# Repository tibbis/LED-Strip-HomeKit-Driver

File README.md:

# Siri Controlled RGB LED-Strip Project
#### By Thibault and Ramtin
### DIY RGB LED strip driver that can be connected to a smart home (HomeKit) using Raspberry Pi and Arduino.

This is a complete DIY guide going through all steps on how to build your own RGB LED Strip Driver that will be able to work together with Apple HomeKit. This will allow you to control the LED-strip wirelessly through the use of Siri. You simply tell Siri to turn on your LED-strip and set the color to e.g. red and through the combined work of the Raspberry Pi, Arduino Uno and a nicely crafted board, the strip will light up in the color of your choice.

_"Hey Siri, put my LED Strip to red."_

### Overview
This illustrates briefly how the complete system works. Basically, by giving Siri or HomeKit on an Apple device a command, the command will be passed to a homebridge server running on the Raspberry Pi. This command will then be passed to a local node.js server that will execute a program which in-turn will send color data wirelessly to an Arduino that is controlling a LED strip.

#### Components used for this project
- RGB-LED Strip (5m with 4 pins)
- Raspberry Pi 3 Model B+
- Arduino UNO
- 2x NRF24L01+ Radio transceiver
- 3x N-Channel MOSFET transistors (IRLB8721, BUZ100 or similar)
- 3x 160 Ohm Resistors
- Circuit Board or breadboard

You may use any type of N-Channel MOSFET as long as they can handle the amount of current that your LED-strip requires per color channel.

### Design of the circuit board for the LED-strip
Depending on your resources you can create your PCB as you want as long you follow the following schematic: (rgb-board.sch)

We will provide an EAGLE file so that it can be milled on a double-sided copper plate using a PCB milling machine, but if you lack the resources, we will also include illustrative pictures of how to do all of this using traditional breadboards.

If you are using a breadboard, this image can be helpful:

The left you see the EAGLE Board file design (rgb-board.brd) and to the right the result with the soldered transistors and resistors:

Now that the LED strip has been prepared with the Arduino, we will take a look at how to hook it up with the RF24-module to enable receiving signals from the Raspberry Pi.
#### Connecting RF24 transceiver to Arduino

This image shows how to connect the wireless transceiver to the Arduino pins.

##### Implementation of code on Arduino
The following code is then implemented into the Arduino. (RGB_DRIVER.ino). Please note that the library RF24.h needs to be installed from e.g: https://github.com/maniacbug/RF24. The pins corresponds to the same pins as the pictures above and the same ID set to the parameter```const uint64_t pipe``` (i.e. in our case: 0xF0F0F0F0E1LL) will be used later on the Raspberry Pi program.

```Arduino
#include "nRF24L01.h"
#include "RF24.h"
#include "RF24_config.h"
#include <SPI.h>
/////////////////////////////-RF24-////////////////////////////////////////
RF24 radio(9, 10); //RF24 pins
const uint64_t pipe = 0xF0F0F0F0E1LL; //ID
unsigned long RGB = 0;
/////////////////////////////////////////////////////////////////////////

//////////////////////////////-RGB-/////////////////////////////////////////
#define REDPIN 5
#define GREENPIN 6
#define BLUEPIN 3
#define FADESPEED 1     // make this higher to slow down fading
int r, g, b, rPrev, gPrev, bPrev, f = 0;
int blueMask = 0xFF0000, greenMask = 0xFF00, redMask = 0xFF; //decoding masks
//////////////////////////////////////////////////////////////////////////

void setup(void) {

  //Radio module setup
  radio.begin();
  radio.openReadingPipe(1, pipe);
  radio.startListening();

  //RGB setup
  pinMode(REDPIN, OUTPUT);
  pinMode(GREENPIN, OUTPUT);
  pinMode(BLUEPIN, OUTPUT);

  //serial Setup
  Serial.begin(9600);
  Serial.println("Started Listening...");
}

void loop(void)
{

  if (radio.available()) { //signal received

    if ( !radio.read(&RGB, sizeof(unsigned long)) ) {
      Serial.println("ACK not received by client.");
    }

    //save previous values
    rPrev = r;
    gPrev = g;
    bPrev = b;
    int[3] prevColors = [rPrev, gPrev, bPrev]; //array with previous color values

    //decode RGB values
    r = (RGB & 0xFF);
    g = ((RGB & 0xFF00) >> 8);
    b = ((RGB & 0xFF0000) >> 16);
    int[3] colors = [r,g,b]; //array with color values

    Serial.print("Received RGB-value: R= "); Serial.print(r); Serial.print(", G= ");
    Serial.print(g); Serial.print(", B= "); Serial.println(b);

    //change color with a smooth transition
    changeColor(colors, prevColors);

  }
}

//change color with a smooth transition
void changeColor(int[3] colors, int[3]prevColors){
  //To determine increase or decrease
  int diffR = colors[0]-prevColors[0];
  int diffG = colors[1]-prevColors[1];
  int diffB = colors[2]-prevColors[2];

  int i = prevColors[0];
  int j = prevColors[1];
  int k = prevColors[2];

  while (i==r && j==g && k==b)
  {
    //Red color
    if (i!=r){
      if (diffR>0) i++;
      else  i--;
      analogWrite(REDPIN, i);

    }
    //Green color
    if (k!=g){
      if (diffG>0) j++;
      else  j--;
      analogWrite(GREENPIN, j);
    }
    //Blue color
    if (k!=b){
      if (diffB>0) k++;
      else  k--;
      analogWrite(BLUEPIN, k);
    }
    delay(FADESPEED);
  }
}
```

### Design and create your own box
We provide you 3D CAD files for a 3D-printable box that fits an Arduino UNO and our PCB that we used. Depending on your circuit board dimensions you may need to create your own box. It needs 3 openings, one for the Arduino USB and DC inputs, and one RGB-LED strip output port (in our case 4 pins). The box should contain the Arduino, circuit board and RF24 transceiver with all its wires.

### Connecting RF24-transceiver to Raspberry Pi 3 B+
When the homebridge and node.js servers are running on the Raspberry Pi they will need to send the data received from HomeKit to the Arduino wirelessly. The image below shows how to connect the RF24 transceiver to Raspberry Pi using GPIO pins.

#### Implementation of code on Raspberry Pi
This C++ program (RF24-remote.cpp + makefile) will be executed by the node.js server and send data through the transceiver. Please note that the library RF24.h must be installed from github (link:TMRh20) for it to compile and install successfully.

```C++
#include <cstdlib>
#include <math.h>
#include <iostream>
#include <sstream>
#include <string>
#include <unistd.h>
#include <RF24/RF24.h>

using namespace std;

//RPi genericpinconnection                                                      $
RF24 radio(25,8);

// Radio pipe addresses for the 2 nodes to communicate.
const uint64_t pipes[2] = { 0xF0F0F0F0E1LL, 0xF0F0F0F0D2LL };

int main(int argc, char** argv){
        unsigned int RGB=atoi(argv[1]);
        cout << "Sending message to LED-Driver…\n";
if (argv[1]){
                // Setup and configure rf radio
                radio.begin();

                // Dump the configuration of the rf unit for debugging
                //radio.printDetails();

        radio.openWritingPipe(pipes[0]);        

                printf("Now sending (RGB: %d)...\n", RGB);
bool ok = radio.write( &RGB, sizeof(unsigned int) ); //send mes$

if (!ok){
                        printf("Failed.\n");
                        return 0;
                }else printf("Message Sent!\n");

        }else printf("Message not sent. No argument was given…\n");
  return 0;
}
```

## Setup of homebridge and node.js servers
Now that all hardware is connected and its corresponding code implemented, the last and a bit tricky part of this guide is left.
#### Install Homebridge
First you will need to install homebridge on your Raspberry Pi by following this guide: link: https://github.com/nfarina/homebridge/wiki/Running-HomeBridge-on-a-Raspberry-Pi.

After you have managed to successfully install homebridge you will need to create a background service for it using serviced. Look at this guide: https://github.com/nfarina/homebridge/wiki/Running-HomeBridge-on-a-Raspberry-Pi#running-homebridge-on-bootup-systemd.

By doing that it will automatically start on boot and as well after eventual crashes.
#### Homebridge Plugins and config.js
You will have to install this plugin: `npm -install http-better-rgb.`

Then you can use this config.js sample code for homebridge:
```javascript
{
        "bridge": {
                "name": "Homebridge",
                "pin": "987-65-431",
                "username": "CC:22:3D:E3:CE:32"
        },

"accessory": "HTTP-RGB",
        "name": "LED Strip",

        "switch": {
            "status": "http://localhost:8080/",
            "powerOn": "http://localhost:8080/",
            "powerOff": "http://localhost:8080/?name=0"
        },

        "brightness": {
            "status": "http://localhost:8080/",
            "url": "http://localhost:8080/?name=%s"
        },

        "color": {
            "status": "http://localhost:8080/",
            "url": "http://localhost:8080/?name=%s",
            "brightness": false
        }
}
]
}
```
You can also add other accessories that you already have in your home that are compatible with various homebridge plugins.

### Node.js Server
Using apache2 and nodejs we can run this server on localhost. This plugins need to be installed for it to work: `npm -install -g hex-rgb`and `npm -install -g http`.

```javascript
#!/usr/bin/env nodejs
var http = require('http');
var url = require('url');
var hexRgb = require('hex-rgb');
const exe = require('child_process').exec;

var hex;
var rgb

var server = http.createServer(function(req, res) {

  var queryData = url.parse(req.url, true).query;
  res.writeHead(200);

  if (queryData.name) {
    hex=queryData.name;
    var rgb_temp=hexRgb(hex); //convert to rgb from hex

    //encode to 24-bit RGB value

    //command to run
    var cmd = 'sudo rf24-RGB-remote ' +rgb;

    exe( cmd ,(error, stdout, stderr) => {
      if (error) {
        throw error;
      }
      //console output
      console.log('--------\nHEX-value: '+hex+", RGB-value: "+rgb_temp+"\n");

      //output on web page
      res.end('RGB-remote server is running! \nRGB-value=' + rgb+'\n\nRF24:');
    });

  }     else { //no argument
    res.end("Server is running! No hex value was given in url... ");
  }

});
server.listen(8080);

console.log('Starting server. Listening on localhost:8080');
```

### [This document is being updated continuously...]

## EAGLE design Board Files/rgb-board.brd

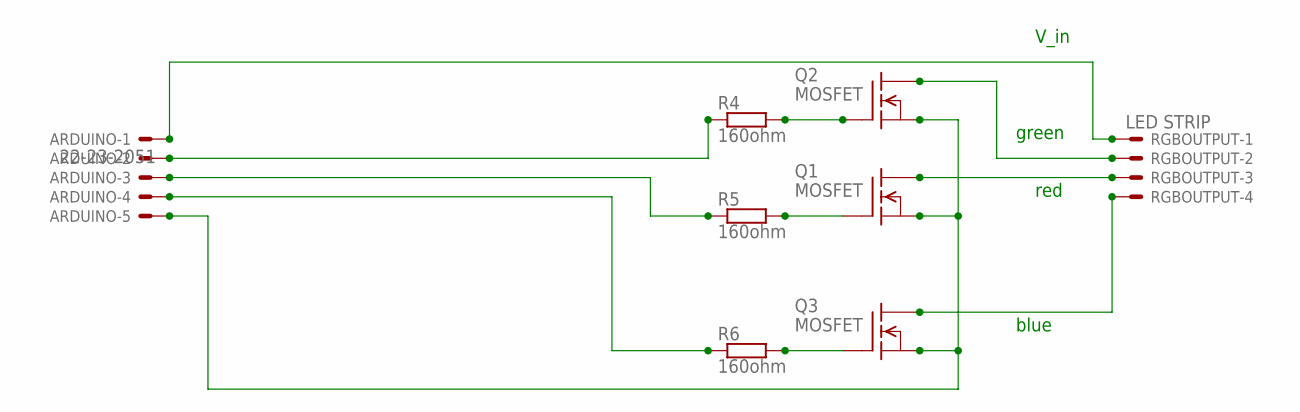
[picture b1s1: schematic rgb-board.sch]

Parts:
ARDUINO: 22-23-2051
Q1, Q2, Q3: MOSFET; TO220
R4, R5, R6: 160ohm; SMS-WAV
RGBOUTPUT: LED STRIP; 22-23-2041

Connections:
BLUE: Q3.2 (D), RGBOUTPUT.4
BLUE2: ARDUINO.4, R6.2
GND: ARDUINO.5, Q1.3 (S), Q2.3 (S), Q3.3 (S)
GREEN: Q2.2 (D), RGBOUTPUT.2
GREEN2: ARDUINO.2, R4.2
unnamed: Q2.1 (G), R4.1
unnamed: Q1.1 (G), R5.1
unnamed: Q3.1 (G), R6.1
RED: Q1.2 (D), RGBOUTPUT.3
RED2: ARDUINO.3, R5.2
VIN: ARDUINO.1, RGBOUTPUT.1

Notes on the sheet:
blue
red
green
V_in

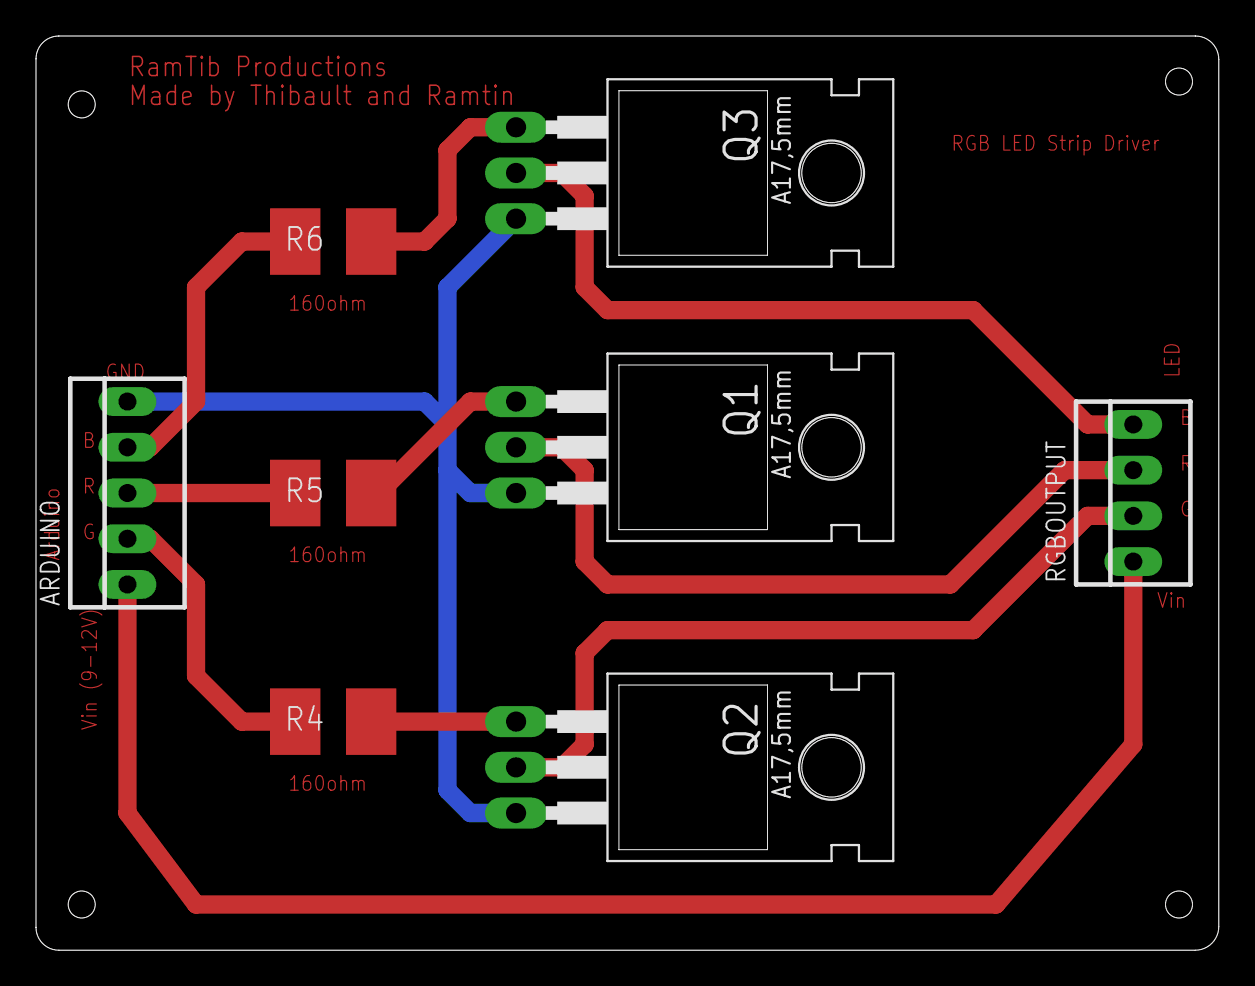
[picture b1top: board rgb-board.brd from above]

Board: 2 copper layers, 65.7 x 50.8 mm, 8 parts (0 on the bottom side), 11 nets.

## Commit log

2017-03-03 components
2017-03-03 uploaded PCB images
    images for readme.md
2017-03-03 EAGLE file
2017-03-03 Arduino code
2017-03-03 CAD models of box, including holes for wires
2017-03-03 RF24 Arduino connections
2017-03-03 images edit
2017-03-03 Some changes
2017-03-03 RF24 library
2017-03-03 Move pictures
2017-03-03 Pictures moved
2017-03-04 Demonstration GIF
2017-03-04 added gif
2017-03-04 demo GIF
2017-03-04 Demo GIF Landscape
2017-03-04 PCB-picture
    PCB result
2017-03-04 PCB picture
    PCB result
2017-03-19 Picture upload
2017-03-19 upload of picture
2017-03-19 Another picture
2017-03-19 Change of names
2017-03-19 updated links and pictures
